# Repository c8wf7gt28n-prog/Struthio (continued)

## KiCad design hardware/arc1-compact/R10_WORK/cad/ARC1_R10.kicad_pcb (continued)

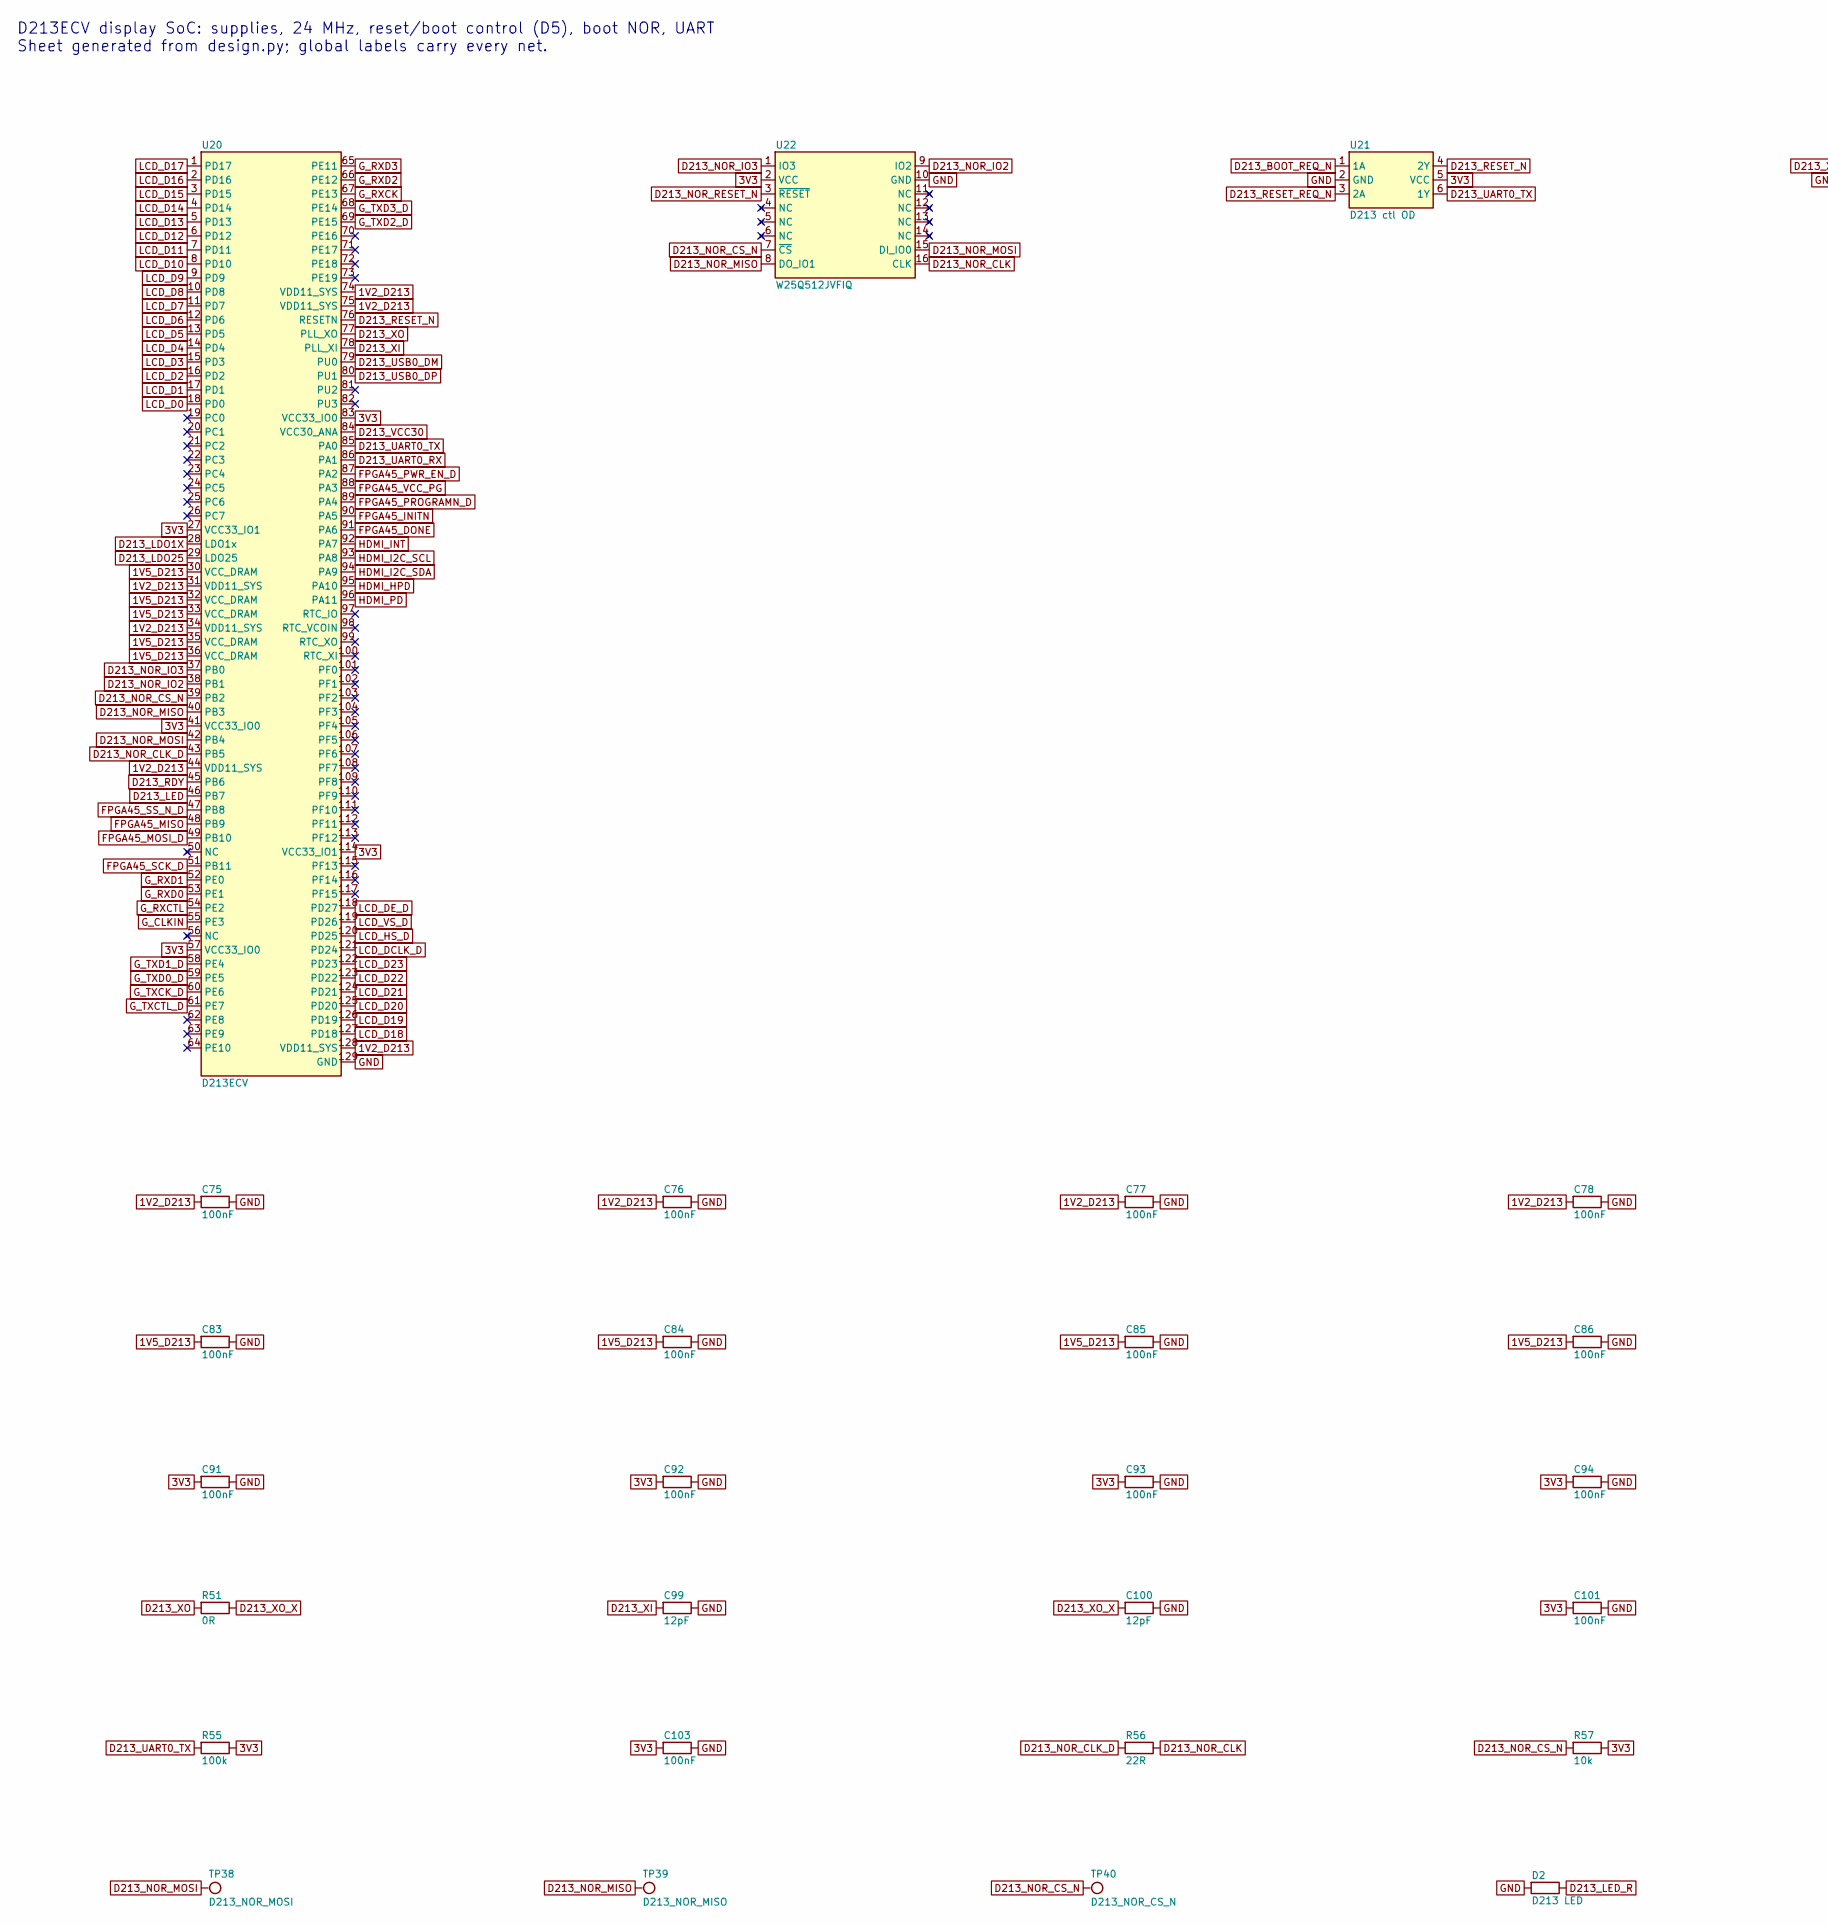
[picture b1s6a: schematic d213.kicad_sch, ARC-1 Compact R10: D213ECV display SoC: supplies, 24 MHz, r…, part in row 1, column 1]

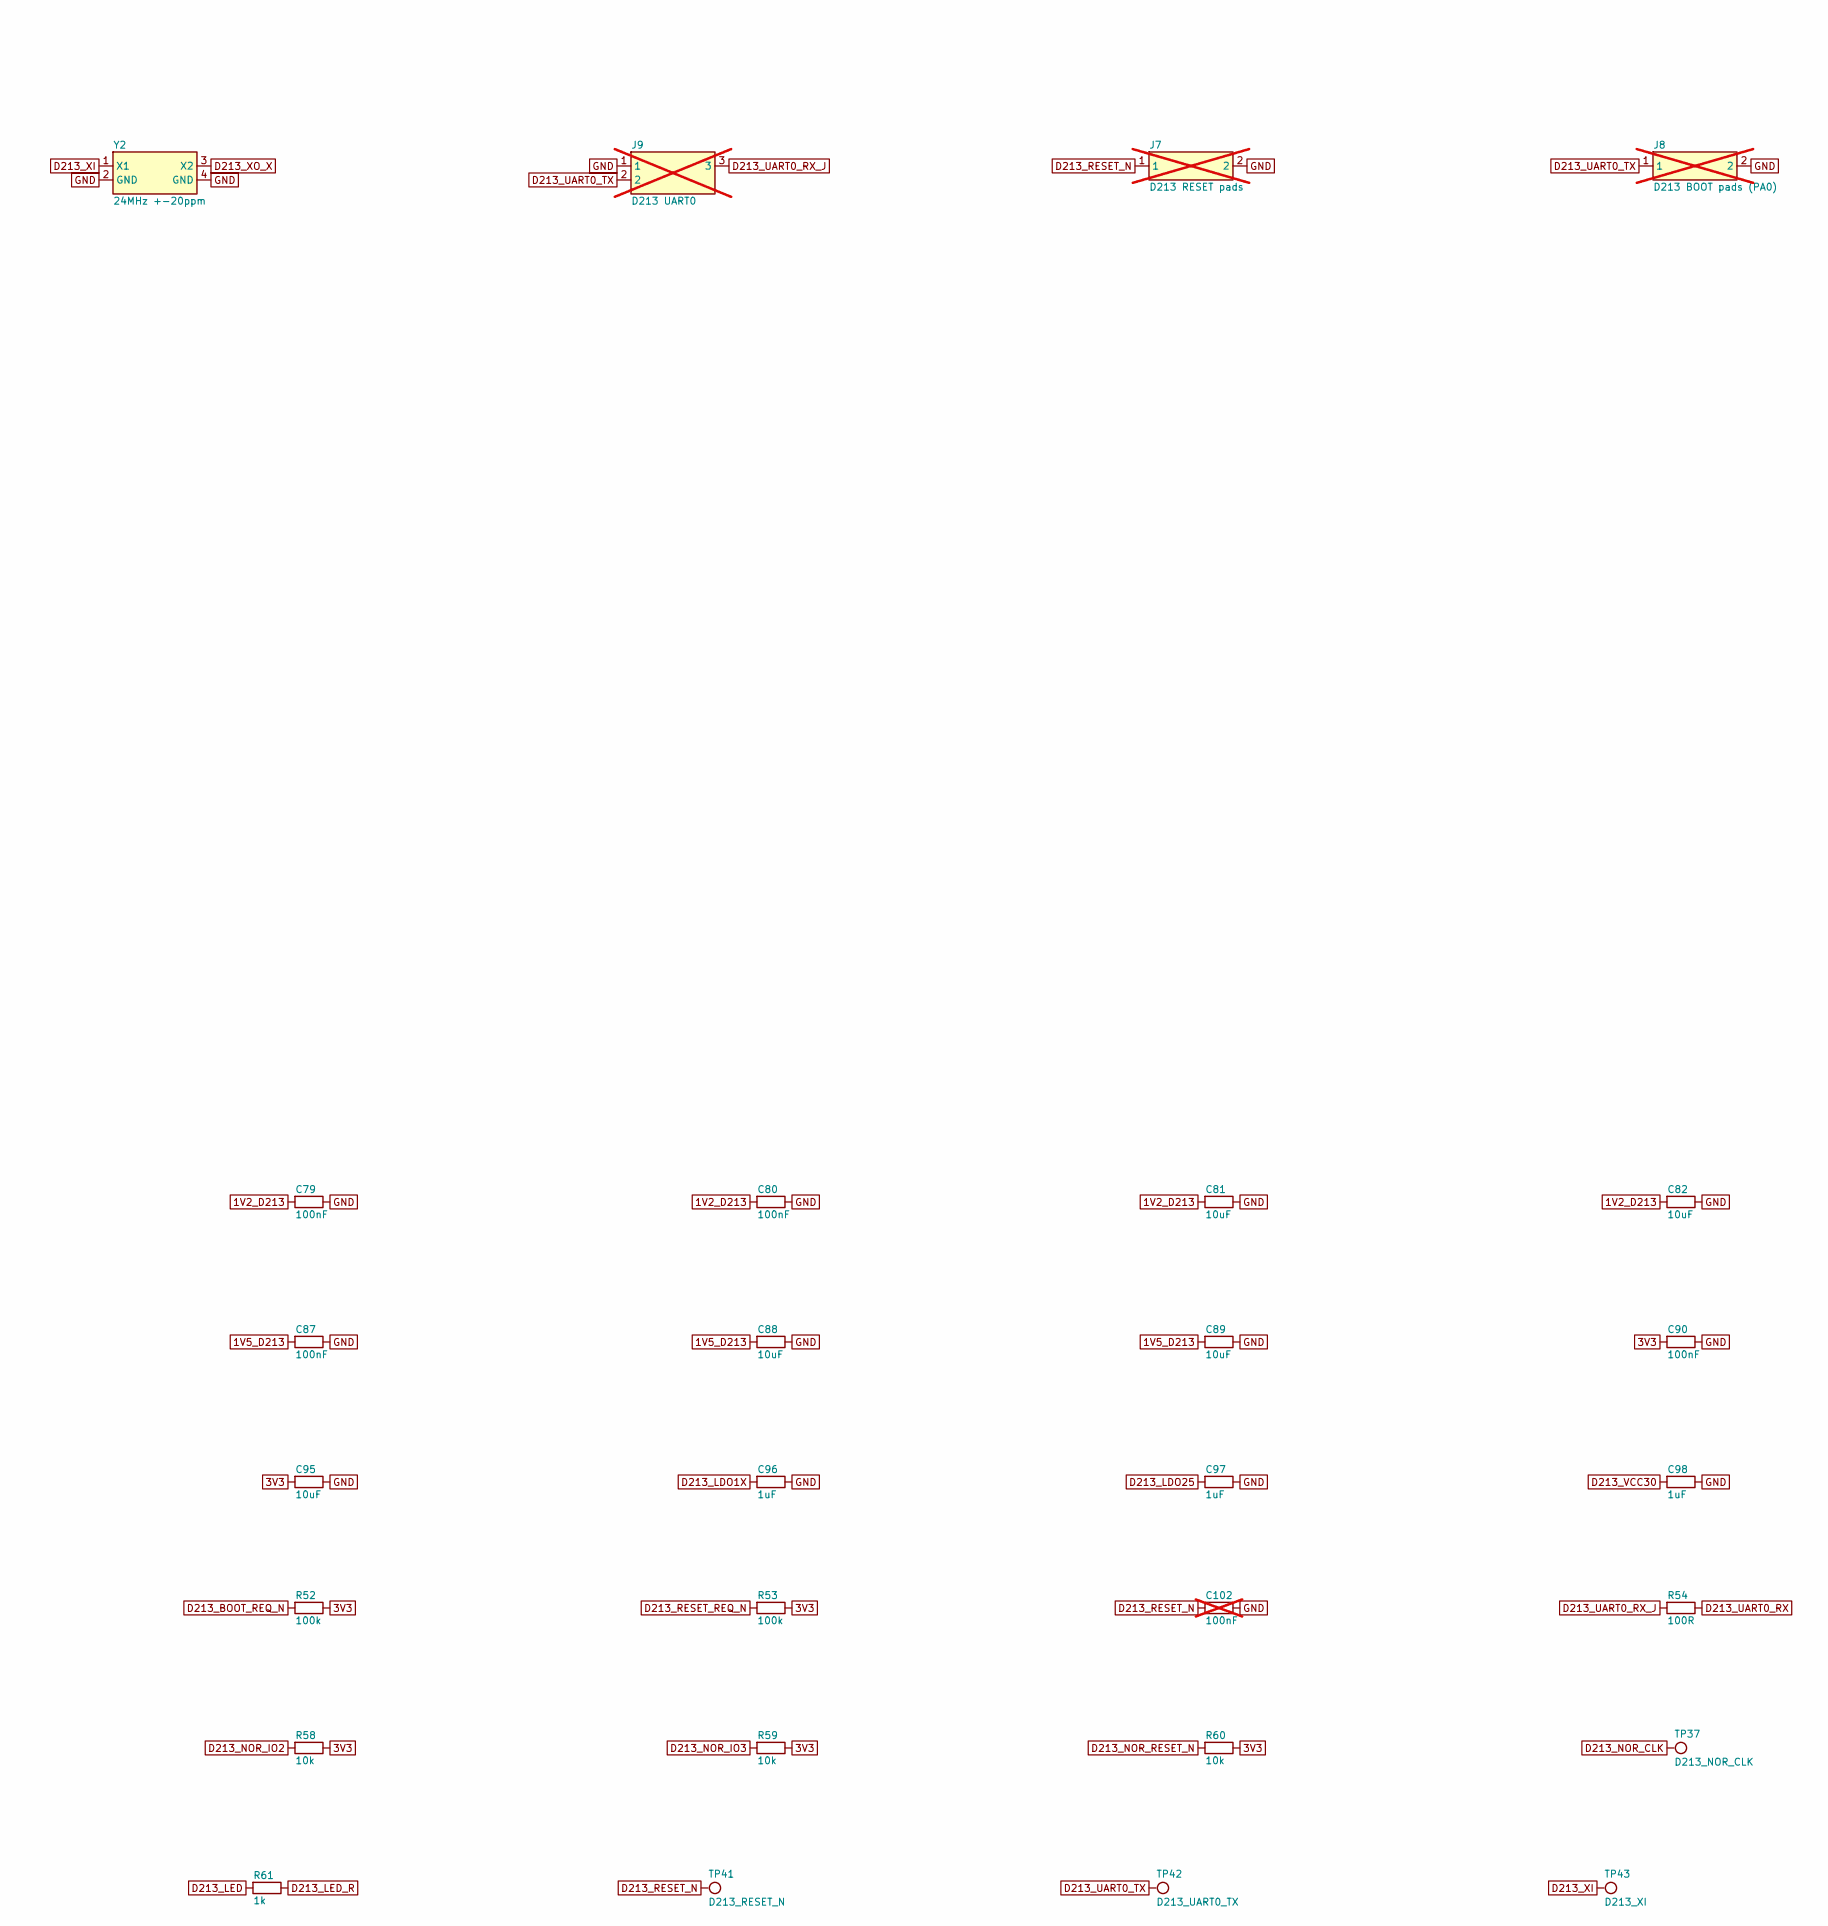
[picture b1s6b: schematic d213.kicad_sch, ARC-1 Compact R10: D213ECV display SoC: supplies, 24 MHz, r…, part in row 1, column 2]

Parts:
C75, C76, C77, C78, C79, C80, C83, C84, C85, C86, C87, C90, C91, C92, C93, C94, C101, C103: 100nF; C_0402_1005Metric; MPN CL05B104KO5NNNC; LCSC C1525
C81, C82, C88, C89, C95: 10uF; C_0603_1608Metric; MPN CL10A106KP8NNNC; LCSC C19702
C96, C97, C98: 1uF; C_0402_1005Metric; MPN CL05A105KA5NQNC; LCSC C52923
C99, C100: 12pF; C_0402_1005Metric; MPN 0402CG120J500NT; LCSC C1547
C102: 100nF; C_0402_1005Metric; MPN CL05B104KO5NNNC; LCSC C1525; not fitted
D2: D213 LED; LED_0603_1608Metric; MPN LED 0603 (MPN TBD)
J7: D213 RESET pads; TestPoint_2Pads_Pitch2.54mm_Drill0.8mm; MPN internal service pad pair; not fitted
J8: D213 BOOT pads (PA0); TestPoint_2Pads_Pitch2.54mm_Drill0.8mm; MPN internal service pad pair; not fitted
J9: D213 UART0; PinHeader_1x03_P2.54mm_Vertical; MPN header 1x3 2.54 (DNP-able); not fitted
R51: 0R; R_0402_1005Metric; MPN 0402WGF0000TCE; LCSC C17168
R52, R53, R55: 100k; R_0402_1005Metric; MPN 0402WGF1003TCE; LCSC C25741
R54: 100R; R_0402_1005Metric
R56: 22R; R_0402_1005Metric; MPN 0402WGF220JTCE; LCSC C25092
R57, R58, R59, R60: 10k; R_0402_1005Metric; MPN 0402WGF1002TCE; LCSC C25744
R61: 1k; R_0402_1005Metric; MPN 0402WGF1001TCE; LCSC C11702
TP37: D213_NOR_CLK; TestPoint_Pad_D1.0mm
TP38: D213_NOR_MOSI; TestPoint_Pad_D1.0mm
TP39: D213_NOR_MISO; TestPoint_Pad_D1.0mm
TP40: D213_NOR_CS_N; TestPoint_Pad_D1.0mm
TP41: D213_RESET_N; TestPoint_Pad_D1.0mm
TP42: D213_UART0_TX; TestPoint_Pad_D1.0mm
TP43: D213_XI; TestPoint_Pad_D1.0mm
U20: D213ECV; ArtInChip_QFN-128-1EP_12.3x12.3mm_P0.35mm_EP7.0x7.0mm; MPN D213ECV
U21: D213 ctl OD; SOT-23-6; MPN SN74LVC2G07DBVR
U22: W25Q512JVFIQ; SOIC-16W_7.5x10.3mm_P1.27mm; MPN W25Q512JVFIQ
Y2: 24MHz +-20ppm; Crystal_SMD_3225-4Pin_3.2x2.5mm; MPN 24 MHz 3225 crystal CL=12 pF +-20 ppm (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

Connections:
1V2_D213: C75.1, C76.1, C77.1, C78.1, C79.1, C80.1, C81.1, C82.1, U20.31 (VDD11_SYS), U20.34 (VDD11_SYS), U20.44 (VDD11_SYS), U20.74 (VDD11_SYS), U20.75 (VDD11_SYS), U20.128 (VDD11_SYS); also elsewhere on the board
1V5_D213: C83.1, C84.1, C85.1, C86.1, C87.1, C88.1, C89.1, U20.30 (VCC_DRAM), U20.32 (VCC_DRAM), U20.33 (VCC_DRAM), U20.35 (VCC_DRAM), U20.36 (VCC_DRAM); also elsewhere on the board
3V3: C90.1, C91.1, C92.1, C93.1, C94.1, C95.1, C101.1, C103.1, R52.2, R53.2, R55.2, R57.2, R58.2, R59.2, R60.2, U20.27 (VCC33_IO1), U20.41 (VCC33_IO0), U20.57 (VCC33_IO0), U20.83 (VCC33_IO0), U20.114 (VCC33_IO1), U21.5 (VCC), U22.2 (VCC); also elsewhere on the board
D213_BOOT_REQ_N: R52.1, U21.1 (1A); also elsewhere on the board
D213_LDO1X: C96.1, U20.28 (LDO1x)
D213_LDO25: C97.1, U20.29 (LDO25)
D213_LED: R61.1, U20.46 (PB7)
D213_LED_R: D2.2 (A), R61.2
D213_NOR_CLK: R56.2, TP37.1, U22.16 (CLK)
D213_NOR_CLK_D: R56.1, U20.43 (PB5)
D213_NOR_CS_N: R57.1, TP40.1, U20.39 (PB2), U22.7 (~CS)
D213_NOR_IO2: R58.1, U20.38 (PB1), U22.9 (IO2)
D213_NOR_IO3: R59.1, U20.37 (PB0), U22.1 (IO3)
D213_NOR_MISO: TP39.1, U20.40 (PB3), U22.8 (DO_IO1)
D213_NOR_MOSI: TP38.1, U20.42 (PB4), U22.15 (DI_IO0)
D213_NOR_RESET_N: R60.1, U22.3 (~RESET)
D213_RDY: U20.45 (PB6); also elsewhere on the board
D213_RESET_N: C102.1, J7.1, TP41.1, U20.76 (RESETN), U21.4 (2Y)
D213_RESET_REQ_N: R53.1, U21.3 (2A); also elsewhere on the board
D213_UART0_RX: R54.2, U20.86 (PA1)
D213_UART0_RX_J: J9.3, R54.1
D213_UART0_TX: J8.1, J9.2, R55.1, TP42.1, U20.85 (PA0), U21.6 (1Y)
D213_USB0_DM: U20.79 (PU0); also elsewhere on the board
D213_USB0_DP: U20.80 (PU1); also elsewhere on the board
D213_VCC30: C98.1, U20.84 (VCC30_ANA)
D213_XI: C99.1, TP43.1, U20.78 (PLL_XI), Y2.1 (X1)
D213_XO: R51.1, U20.77 (PLL_XO)
D213_XO_X: C100.1, R51.2, Y2.3 (X2)
FPGA45_DONE: U20.91 (PA6); also elsewhere on the board
FPGA45_INITN: U20.90 (PA5); also elsewhere on the board
FPGA45_MISO: U20.48 (PB9); also elsewhere on the board
FPGA45_MOSI_D: U20.49 (PB10); also elsewhere on the board
FPGA45_PROGRAMN_D: U20.89 (PA4); also elsewhere on the board
FPGA45_PWR_EN_D: U20.87 (PA2); also elsewhere on the board
FPGA45_SCK_D: U20.51 (PB11); also elsewhere on the board
FPGA45_SS_N_D: U20.47 (PB8); also elsewhere on the board
FPGA45_VCC_PG: U20.88 (PA3); also elsewhere on the board
GND: C75.2, C76.2, C77.2, C78.2, C79.2, C80.2, C81.2, C82.2, C83.2, C84.2, C85.2, C86.2, C87.2, C88.2, C89.2, C90.2, C91.2, C92.2, C93.2, C94.2, C95.2, C96.2, C97.2, C98.2, C99.2, C100.2, C101.2, C102.2, C103.2, D2.1 (K), J7.2, J8.2, J9.1, U20.129 (GND), U21.2 (GND), U22.10 (GND), Y2.2 (GND), Y2.4 (GND); also elsewhere on the board
G_CLKIN: U20.55 (PE3); also elsewhere on the board
G_RXCK: U20.67 (PE13); also elsewhere on the board
G_RXCTL: U20.54 (PE2); also elsewhere on the board
G_RXD0: U20.53 (PE1); also elsewhere on the board
G_RXD1: U20.52 (PE0); also elsewhere on the board
G_RXD2: U20.66 (PE12); also elsewhere on the board
G_RXD3: U20.65 (PE11); also elsewhere on the board
G_TXCK_D: U20.60 (PE6); also elsewhere on the board
G_TXCTL_D: U20.61 (PE7); also elsewhere on the board
G_TXD0_D: U20.59 (PE5); also elsewhere on the board
G_TXD1_D: U20.58 (PE4); also elsewhere on the board
G_TXD2_D: U20.69 (PE15); also elsewhere on the board
G_TXD3_D: U20.68 (PE14); also elsewhere on the board
HDMI_HPD: U20.95 (PA10); also elsewhere on the board
HDMI_I2C_SCL: U20.93 (PA8); also elsewhere on the board
HDMI_I2C_SDA: U20.94 (PA9); also elsewhere on the board
HDMI_INT: U20.92 (PA7); also elsewhere on the board
HDMI_PD: U20.96 (PA11); also elsewhere on the board
LCD_D0: U20.18 (PD0); also elsewhere on the board
LCD_D1: U20.17 (PD1); also elsewhere on the board
LCD_D2: U20.16 (PD2); also elsewhere on the board
LCD_D3: U20.15 (PD3); also elsewhere on the board
LCD_D4: U20.14 (PD4); also elsewhere on the board
LCD_D5: U20.13 (PD5); also elsewhere on the board
LCD_D6: U20.12 (PD6); also elsewhere on the board
LCD_D7: U20.11 (PD7); also elsewhere on the board
LCD_D8: U20.10 (PD8); also elsewhere on the board
LCD_D9: U20.9 (PD9); also elsewhere on the board
LCD_D10: U20.8 (PD10); also elsewhere on the board
LCD_D11: U20.7 (PD11); also elsewhere on the board
LCD_D12: U20.6 (PD12); also elsewhere on the board
LCD_D13: U20.5 (PD13); also elsewhere on the board
LCD_D14: U20.4 (PD14); also elsewhere on the board
LCD_D15: U20.3 (PD15); also elsewhere on the board
LCD_D16: U20.2 (PD16); also elsewhere on the board
LCD_D17: U20.1 (PD17); also elsewhere on the board
LCD_D18: U20.127 (PD18); also elsewhere on the board
LCD_D19: U20.126 (PD19); also elsewhere on the board
LCD_D20: U20.125 (PD20); also elsewhere on the board
LCD_D21: U20.124 (PD21); also elsewhere on the board
LCD_D22: U20.123 (PD22); also elsewhere on the board
LCD_D23: U20.122 (PD23); also elsewhere on the board
LCD_DCLK_D: U20.121 (PD24); also elsewhere on the board
LCD_DE_D: U20.118 (PD27); also elsewhere on the board
LCD_HS_D: U20.120 (PD25); also elsewhere on the board
LCD_VS_D: U20.119 (PD26); also elsewhere on the board

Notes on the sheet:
D213ECV display SoC: supplies, 24 MHz, reset/boot control (D5), boot NOR, UART Sheet generated from design.py; global labels carry every net.

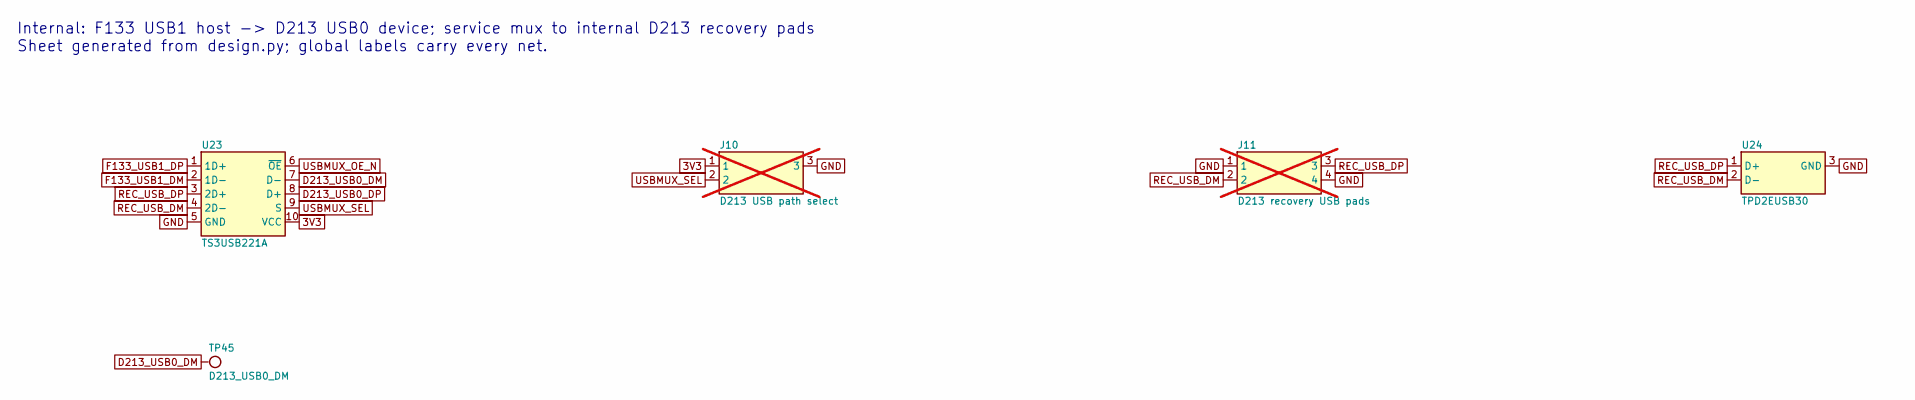
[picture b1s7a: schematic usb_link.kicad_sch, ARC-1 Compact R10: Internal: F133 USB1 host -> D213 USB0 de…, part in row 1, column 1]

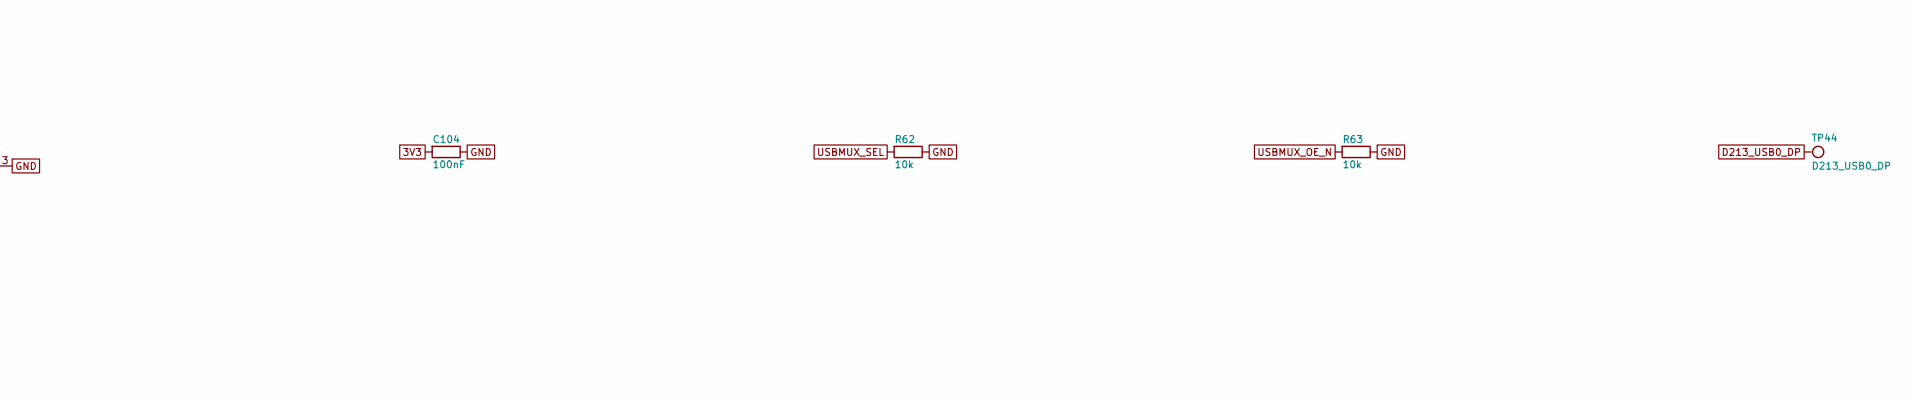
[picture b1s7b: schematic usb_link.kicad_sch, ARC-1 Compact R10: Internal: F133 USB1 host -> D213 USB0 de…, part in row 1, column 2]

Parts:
C104: 100nF; C_0402_1005Metric; MPN CL05B104KO5NNNC; LCSC C1525
J10: D213 USB path select; PinHeader_1x03_P2.54mm_Vertical; MPN header 1x3 2.54 (DNP-able); not fitted
J11: D213 recovery USB pads; PinHeader_1x04_P2.54mm_Vertical; MPN internal service pads (not populated); not fitted
R62, R63: 10k; R_0402_1005Metric; MPN 0402WGF1002TCE; LCSC C25744
TP44: D213_USB0_DP; TestPoint_Pad_D1.0mm
TP45: D213_USB0_DM; TestPoint_Pad_D1.0mm
U23: TS3USB221A; Texas_UQFN-10_1.5x2mm_P0.5mm; MPN TS3USB221ARSER
U24: TPD2EUSB30; SLIM4_FP_U11_TPD2EUSB30_DRT3; MPN TPD2EUSB30DRTR; LCSC C97502

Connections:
3V3: C104.1, J10.1, U23.10 (VCC); also elsewhere on the board
D213_USB0_DM: TP45.1, U23.7 (D-); also elsewhere on the board
D213_USB0_DP: TP44.1, U23.8 (D+); also elsewhere on the board
F133_USB1_DM: U23.2 (1D-); also elsewhere on the board
F133_USB1_DP: U23.1 (1D+); also elsewhere on the board
GND: C104.2, J10.3, J11.1, J11.4, R62.2, R63.2, U23.5 (GND), U24.3 (GND); also elsewhere on the board
REC_USB_DM: J11.2, U23.4 (2D-), U24.2 (D-)
REC_USB_DP: J11.3, U23.3 (2D+), U24.1 (D+)
USBMUX_OE_N: R63.1, U23.6 (~OE)
USBMUX_SEL: J10.2, R62.1, U23.9 (S)

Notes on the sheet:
Internal: F133 USB1 host -> D213 USB0 device; service mux to internal D213 recovery pads Sheet generated from design.py; global labels carry every net.

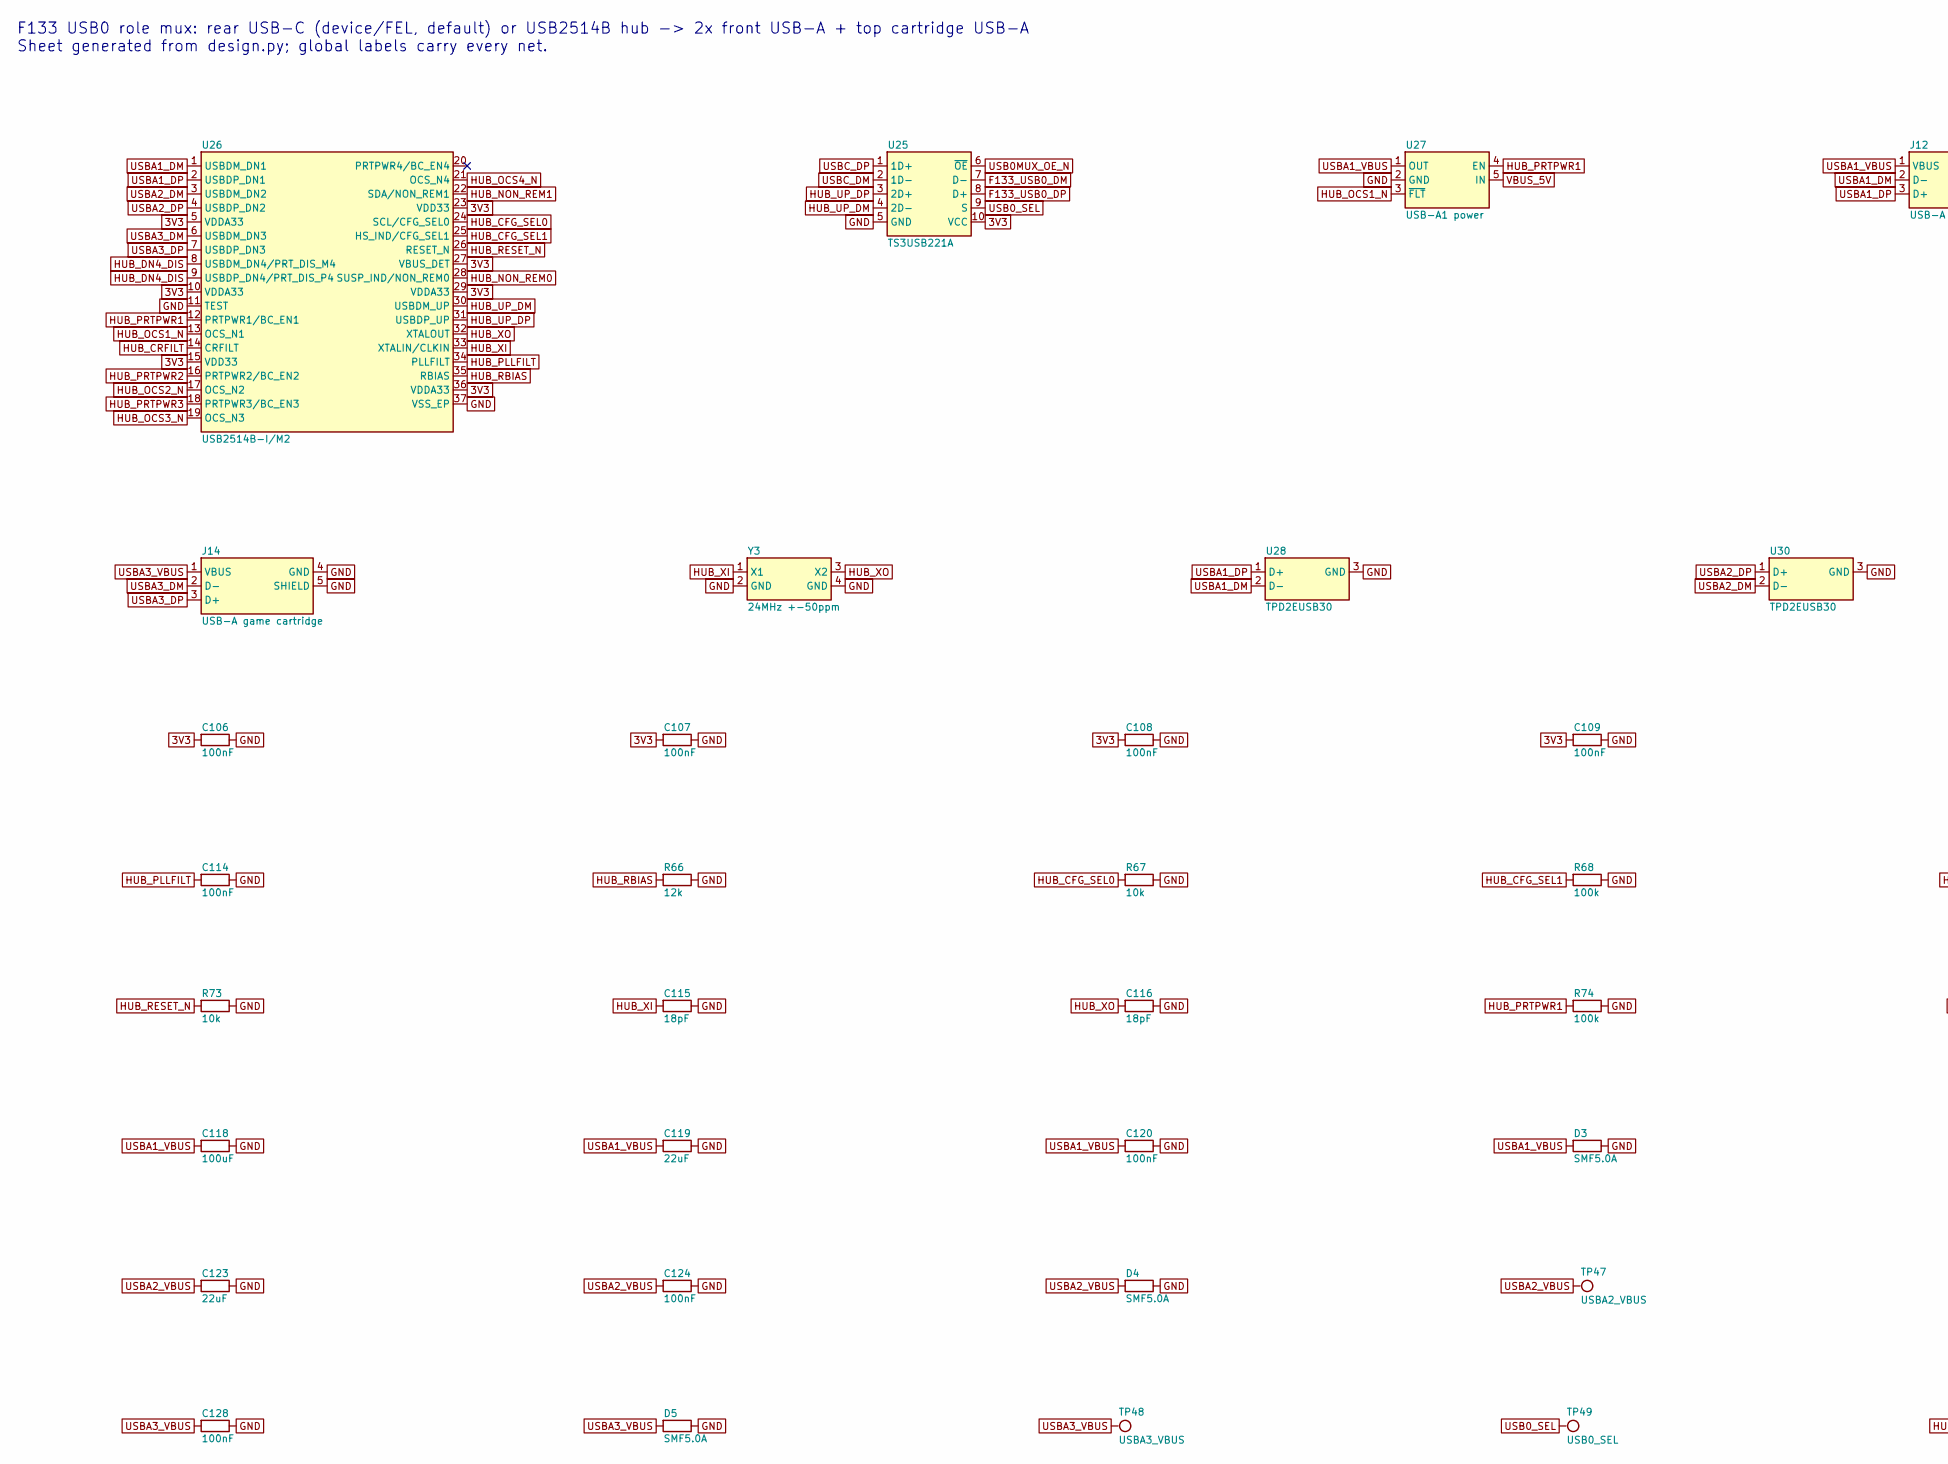
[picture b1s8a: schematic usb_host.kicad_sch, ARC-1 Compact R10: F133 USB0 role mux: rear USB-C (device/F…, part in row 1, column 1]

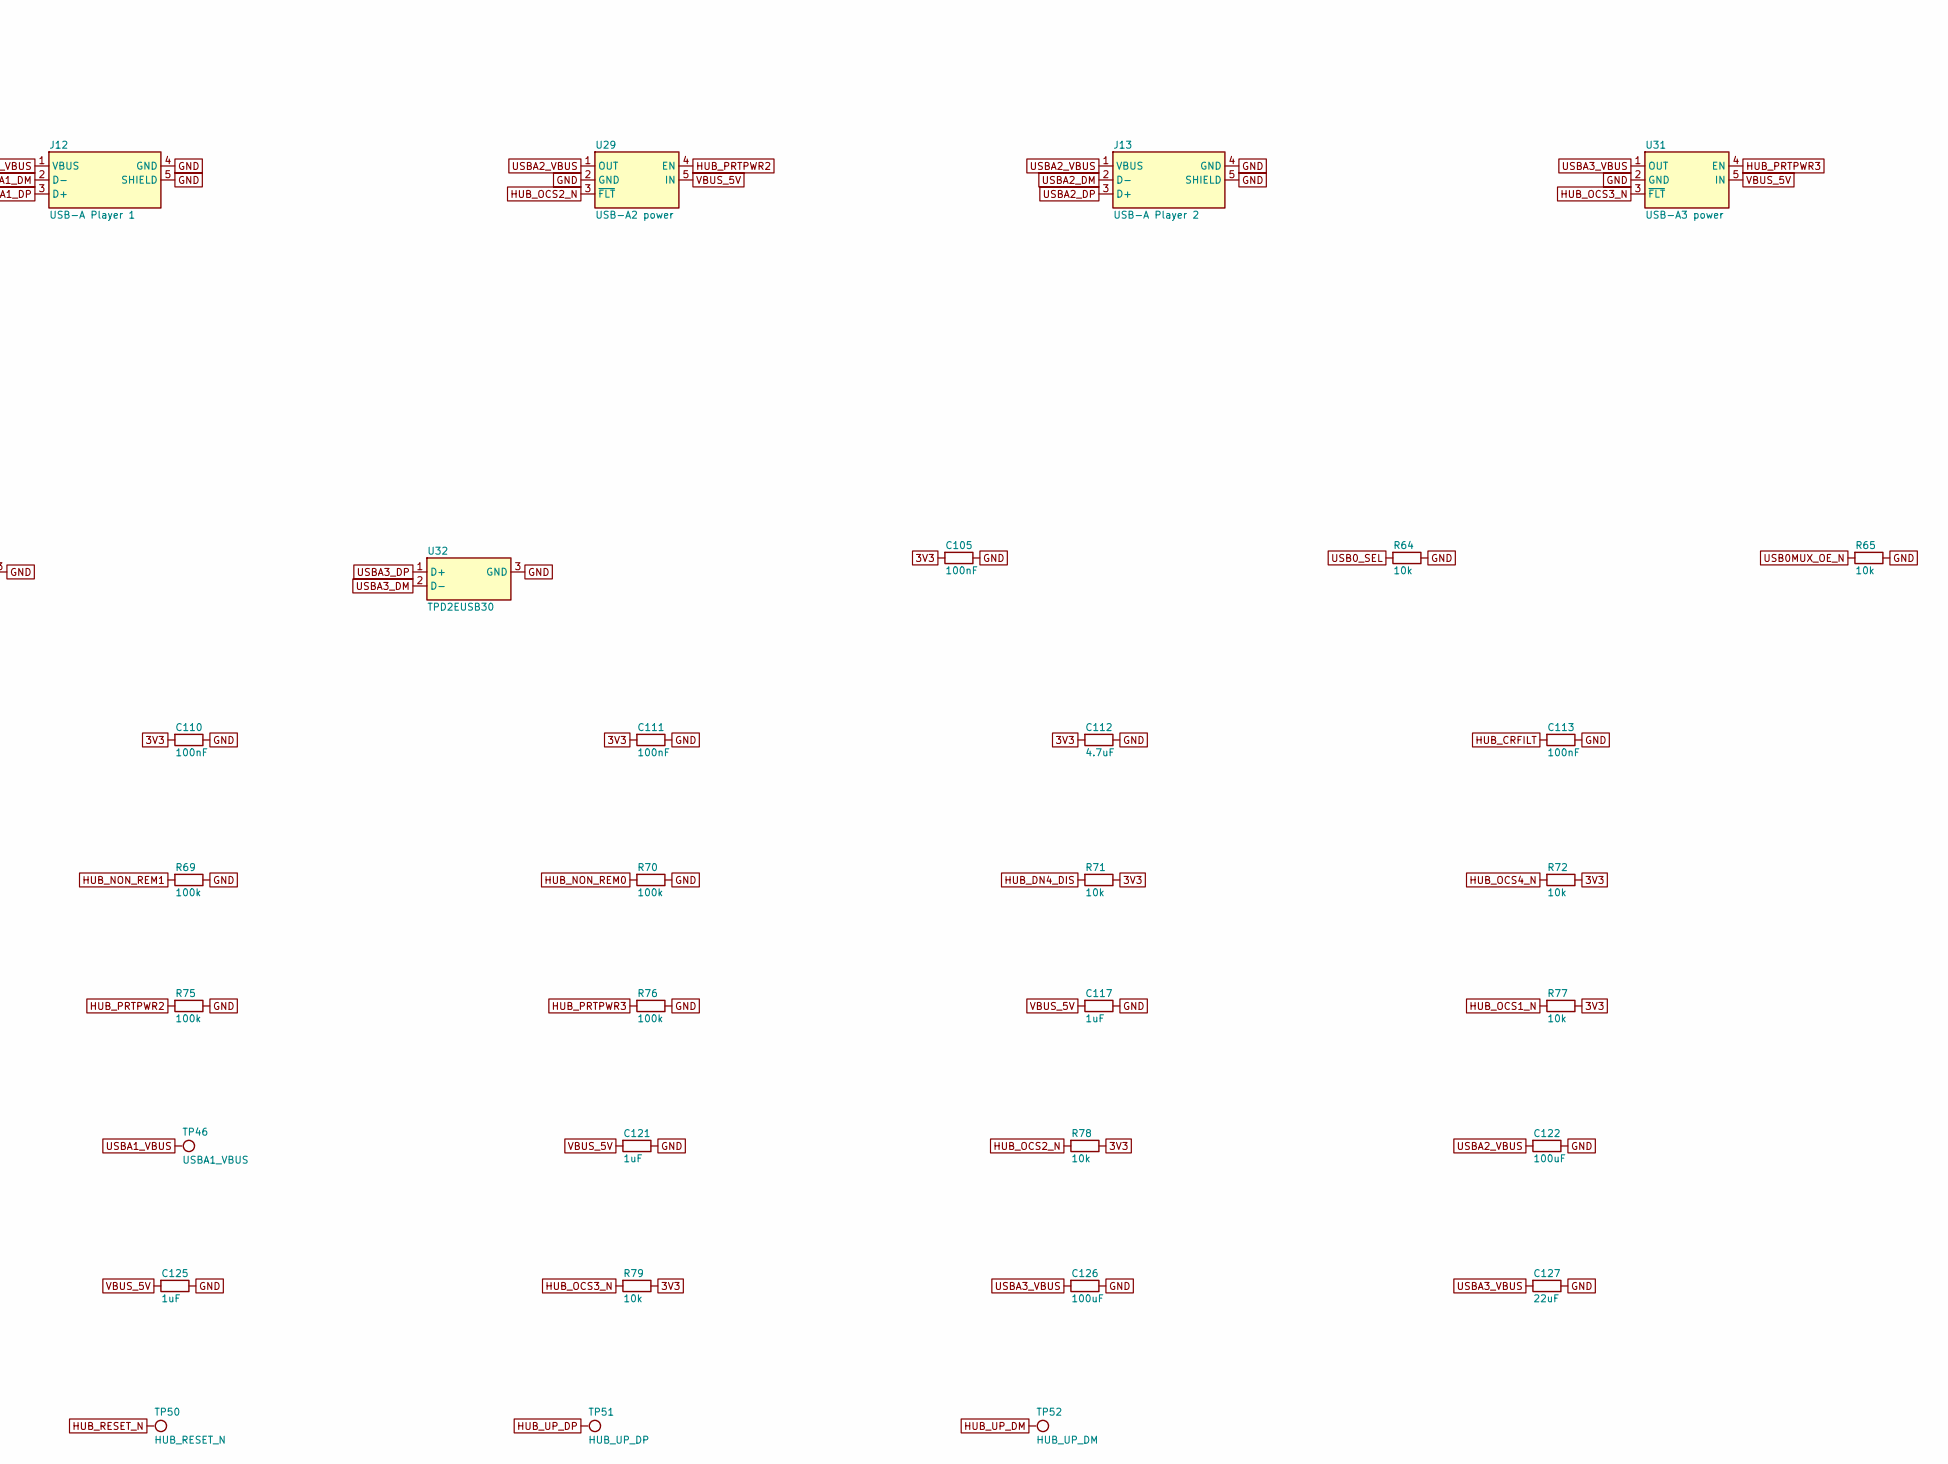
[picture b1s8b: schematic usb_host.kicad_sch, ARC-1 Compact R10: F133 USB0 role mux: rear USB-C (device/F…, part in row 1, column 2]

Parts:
C105, C106, C107, C108, C109, C110, C111, C113, C114, C120, C124, C128: 100nF; C_0402_1005Metric; MPN CL05B104KO5NNNC; LCSC C1525
C112: 4.7uF; C_0603_1608Metric; MPN CL10A475KO8NNNC; LCSC C19666
C115, C116: 18pF; C_0402_1005Metric
C117, C121, C125: 1uF; C_0402_1005Metric; MPN CL05A105KA5NQNC; LCSC C52923
C118, C122, C126: 100uF; C_1210_3225Metric
C119, C123, C127: 22uF; C_0805_2012Metric; MPN CL21A226MQQNNNE; LCSC C5674
D3, D4, D5: SMF5.0A; D_SMF; MPN SMF5.0A
J12: USB-A Player 1; USB_A_Molex_67643_Horizontal; MPN 67643-0910
J13: USB-A Player 2; USB_A_Molex_67643_Horizontal; MPN 67643-0910
J14: USB-A game cartridge; USB_A_Molex_105057_Vertical; MPN 1050570001
R64, R65, R67, R71, R72, R73, R77, R78, R79: 10k; R_0402_1005Metric; MPN 0402WGF1002TCE; LCSC C25744
R66: 12k; R_0402_1005Metric
R68, R69, R70, R74, R75, R76: 100k; R_0402_1005Metric; MPN 0402WGF1003TCE; LCSC C25741
TP46: USBA1_VBUS; TestPoint_Pad_D1.0mm
TP47: USBA2_VBUS; TestPoint_Pad_D1.0mm
TP48: USBA3_VBUS; TestPoint_Pad_D1.0mm
TP49: USB0_SEL; TestPoint_Pad_D1.0mm
TP50: HUB_RESET_N; TestPoint_Pad_D1.0mm
TP51: HUB_UP_DP; TestPoint_Pad_D1.0mm
TP52: HUB_UP_DM; TestPoint_Pad_D1.0mm
U25: TS3USB221A; Texas_UQFN-10_1.5x2mm_P0.5mm; MPN TS3USB221ARSER
U26: USB2514B-I/M2; QFN-36-1EP_6x6mm_P0.5mm_EP3.7x3.7mm_ThermalVias; MPN USB2514B-I/M2
U27: USB-A1 power; SOT-23-5; MPN TPS2051CDBVR
U28, U30, U32: TPD2EUSB30; SLIM4_FP_U11_TPD2EUSB30_DRT3; MPN TPD2EUSB30DRTR; LCSC C97502
U29: USB-A2 power; SOT-23-5; MPN TPS2051CDBVR
U31: USB-A3 power; SOT-23-5; MPN TPS2051CDBVR
Y3: 24MHz +-50ppm; Crystal_SMD_3225-4Pin_3.2x2.5mm; MPN 24 MHz 3225 crystal CL=12 pF +-20 ppm (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

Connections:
3V3: C105.1, C106.1, C107.1, C108.1, C109.1, C110.1, C111.1, C112.1, R71.2, R72.2, R77.2, R78.2, R79.2, U25.10 (VCC), U26.5 (VDDA33), U26.10 (VDDA33), U26.15 (VDD33), U26.23 (VDD33), U26.27 (VBUS_DET), U26.29 (VDDA33), U26.36 (VDDA33); also elsewhere on the board
F133_USB0_DM: U25.7 (D-); also elsewhere on the board
F133_USB0_DP: U25.8 (D+); also elsewhere on the board
GND: C105.2, C106.2, C107.2, C108.2, C109.2, C110.2, C111.2, C112.2, C113.2, C114.2, C115.2, C116.2, C117.2, C118.2, C119.2, C120.2, C121.2, C122.2, C123.2, C124.2, C125.2, C126.2, C127.2, C128.2, D3.2 (A), D4.2 (A), D5.2 (A), J12.4 (GND), J12.5 (SHIELD), J13.4 (GND), J13.5 (SHIELD), J14.4 (GND), J14.5 (SHIELD), R64.2, R65.2, R66.2, R67.2, R68.2, R69.2, R70.2, R73.2, R74.2, R75.2, R76.2, U25.5 (GND), U26.11 (TEST), U26.37 (VSS_EP), U27.2 (GND), U28.3 (GND), U29.2 (GND), U30.3 (GND), U31.2 (GND), U32.3 (GND), Y3.2 (GND), Y3.4 (GND); also elsewhere on the board
HUB_CFG_SEL0: R67.1, U26.24 (SCL/CFG_SEL0)
HUB_CFG_SEL1: R68.1, U26.25 (HS_IND/CFG_SEL1)
HUB_CRFILT: C113.1, U26.14 (CRFILT)
HUB_DN4_DIS: R71.1, U26.8 (USBDM_DN4/PRT_DIS_M4), U26.9 (USBDP_DN4/PRT_DIS_P4)
HUB_NON_REM0: R70.1, U26.28 (SUSP_IND/NON_REM0)
HUB_NON_REM1: R69.1, U26.22 (SDA/NON_REM1)
HUB_OCS1_N: R77.1, U26.13 (OCS_N1), U27.3 (~FLT)
HUB_OCS2_N: R78.1, U26.17 (OCS_N2), U29.3 (~FLT)
HUB_OCS3_N: R79.1, U26.19 (OCS_N3), U31.3 (~FLT)
HUB_OCS4_N: R72.1, U26.21 (OCS_N4)
HUB_PLLFILT: C114.1, U26.34 (PLLFILT)
HUB_PRTPWR1: R74.1, U26.12 (PRTPWR1/BC_EN1), U27.4 (EN)
HUB_PRTPWR2: R75.1, U26.16 (PRTPWR2/BC_EN2), U29.4 (EN)
HUB_PRTPWR3: R76.1, U26.18 (PRTPWR3/BC_EN3), U31.4 (EN)
HUB_RBIAS: R66.1, U26.35 (RBIAS)
HUB_RESET_N: R73.1, TP50.1, U26.26 (RESET_N); also elsewhere on the board
HUB_UP_DM: TP52.1, U25.4 (2D-), U26.30 (USBDM_UP)
HUB_UP_DP: TP51.1, U25.3 (2D+), U26.31 (USBDP_UP)
HUB_XI: C115.1, U26.33 (XTALIN/CLKIN), Y3.1 (X1)
HUB_XO: C116.1, U26.32 (XTALOUT), Y3.3 (X2)
USB0MUX_OE_N: R65.1, U25.6 (~OE)
USB0_SEL: R64.1, TP49.1, U25.9 (S); also elsewhere on the board
USBA1_DM: J12.2 (D-), U26.1 (USBDM_DN1), U28.2 (D-)
USBA1_DP: J12.3 (D+), U26.2 (USBDP_DN1), U28.1 (D+)
USBA1_VBUS: C118.1, C119.1, C120.1, D3.1 (K), J12.1 (VBUS), TP46.1, U27.1 (OUT)
USBA2_DM: J13.2 (D-), U26.3 (USBDM_DN2), U30.2 (D-)
USBA2_DP: J13.3 (D+), U26.4 (USBDP_DN2), U30.1 (D+)
USBA2_VBUS: C122.1, C123.1, C124.1, D4.1 (K), J13.1 (VBUS), TP47.1, U29.1 (OUT)
USBA3_DM: J14.2 (D-), U26.6 (USBDM_DN3), U32.2 (D-)
USBA3_DP: J14.3 (D+), U26.7 (USBDP_DN3), U32.1 (D+)
USBA3_VBUS: C126.1, C127.1, C128.1, D5.1 (K), J14.1 (VBUS), TP48.1, U31.1 (OUT)
USBC_DM: U25.2 (1D-); also elsewhere on the board
USBC_DP: U25.1 (1D+); also elsewhere on the board
VBUS_5V: C117.1, C121.1, C125.1, U27.5 (IN), U29.5 (IN), U31.5 (IN); also elsewhere on the board

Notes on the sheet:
F133 USB0 role mux: rear USB-C (device/FEL, default) or USB2514B hub -> 2x front USB-A + top cartridge USB-A Sheet generated from design.py; global labels carry every net.
